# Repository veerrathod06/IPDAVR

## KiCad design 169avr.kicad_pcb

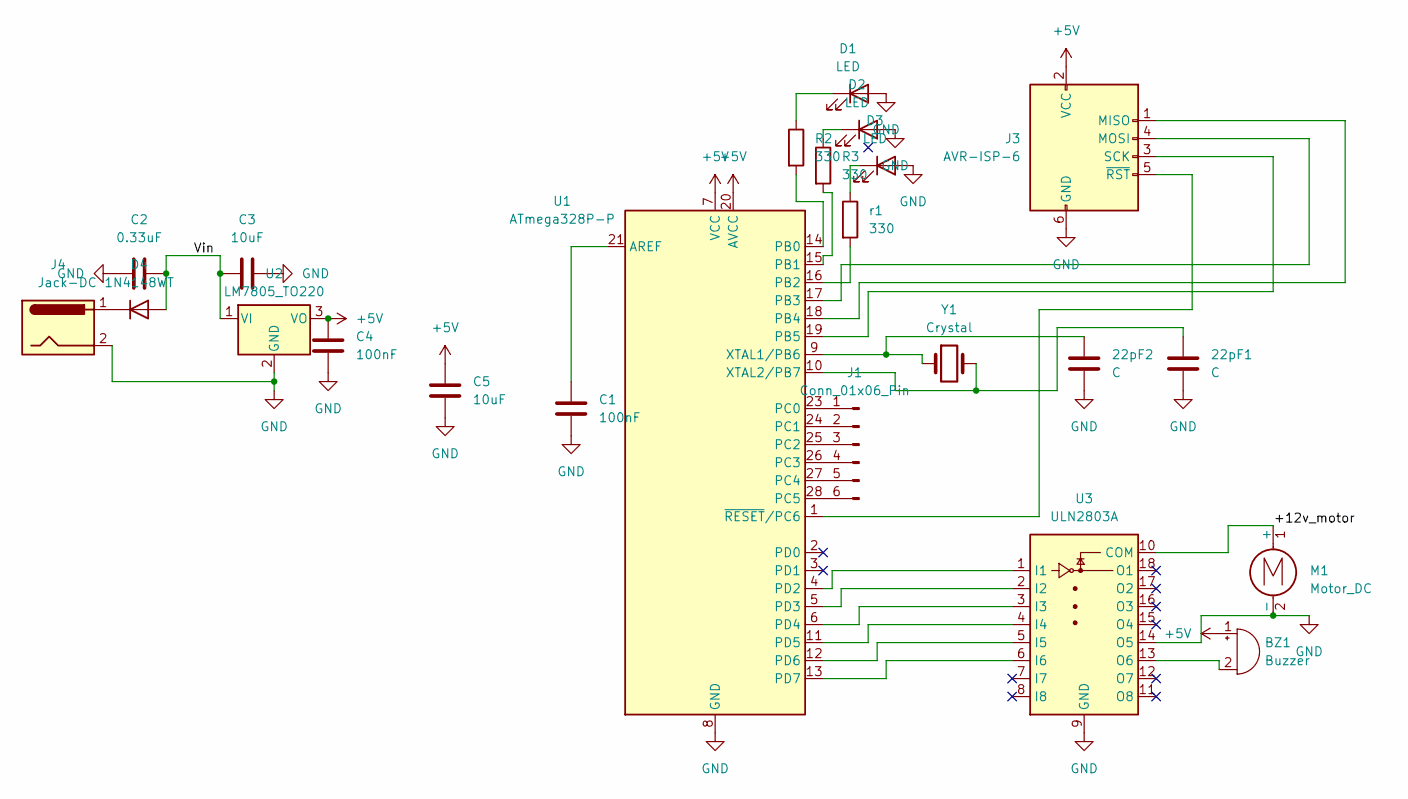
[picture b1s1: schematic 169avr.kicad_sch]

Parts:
22pF1, 22pF2: C; C_Disc_D5.0mm_W2.5mm_P5.00mm
BZ1: Buzzer; Buzzer_12x9.5RM7.6
C1, C4: 100nF; C_Disc_D5.0mm_W2.5mm_P5.00mm
C2: 0.33uF; CP_Radial_D5.0mm_P2.00mm
C3, C5: 10uF; CP_Radial_D5.0mm_P2.00mm
D1, D2, D3: LED; LED_D5.0mm_IRBlack
D4: 1N4148WT; D_DO-35_SOD27_P7.62mm_Horizontal
J1: Conn_01x06_Pin; PinHeader_1x06_P2.54mm_Vertical
J3: AVR-ISP-6; PinHeader_2x03_P2.54mm_Vertical
J4: Jack-DC; BarrelJack_SwitchcraftConxall_RAPC10U_Horizontal
M1: Motor_DC; TerminalBlock_Phoenix_MKDS-1-2-3.81_1x02_P3.81mm_Horizontal
R2: 330; R_Axial_DIN0204_L3.6mm_D1.6mm_P1.90mm_Vertical
R3: 330; R_Axial_DIN0204_L3.6mm_D1.6mm_P2.54mm_Vertical
U1: ATmega328P-P; DIP-28_W7.62mm
U2: LM7805_TO220; TO-220-3_Vertical
U3: ULN2803A; DIP-18_W7.62mm
Y1: Crystal; Crystal_HC49-U_Vertical
r1: 330; R_Axial_DIN0207_L6.3mm_D2.5mm_P15.24mm_Horizontal

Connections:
+5V: BZ1.1 (+), C4.1, C5.1, J3.2 (VCC), U1.7 (VCC), U1.20 (AVCC), U2.3 (VO)
/+12v_motor: M1.1 (+), U3.10 (COM)
/Vin: C2.1, C3.1, D4.2 (A), U2.1 (VI)
GND: 22pF1.2, 22pF2.2, C1.2, C2.2, C3.2, C4.2, C5.2, D1.2 (A), D2.2 (A), D3.2 (A), J3.6 (GND), J4.2, M1.2 (-), U1.8 (GND), U1.22 (GND), U2.2 (GND), U3.9 (GND), U3.14 (O5)
unnamed: BZ1.2 (-), U3.13 (O6)
unnamed: D1.1 (K), R2.1
unnamed: D2.1 (K), R3.1
unnamed: D3.1 (K), r1.1
unnamed: D4.1 (K), J4.1
unnamed: J1.1, U1.23 (PC0)
unnamed: J1.2, U1.24 (PC1)
unnamed: J1.3, U1.25 (PC2)
unnamed: J1.4, U1.26 (PC3)
unnamed: J1.5, U1.27 (PC4)
unnamed: J1.6, U1.28 (PC5)
unnamed: J3.1 (MISO), U1.18 (PB4)
unnamed: J3.4 (MOSI), U1.17 (PB3)
unnamed: J3.3 (SCK), U1.19 (PB5)
unnamed: J3.5 (~RST), U1.1 (~RESET/PC6)
unnamed: C1.1, U1.21 (AREF)
unnamed: R2.2, U1.14 (PB0)
unnamed: R3.2, U1.15 (PB1)
unnamed: U1.16 (PB2), r1.2
unnamed: U1.4 (PD2), U3.1 (I1)
unnamed: U1.5 (PD3), U3.2 (I2)
unnamed: U1.6 (PD4), U3.3 (I3)
unnamed: U1.11 (PD5), U3.4 (I4)
unnamed: U1.12 (PD6), U3.5 (I5)
unnamed: U1.13 (PD7), U3.6 (I6)
unnamed: 22pF2.1, U1.9 (XTAL1/PB6), Y1.1
unnamed: 22pF1.1, U1.10 (XTAL2/PB7), Y1.2

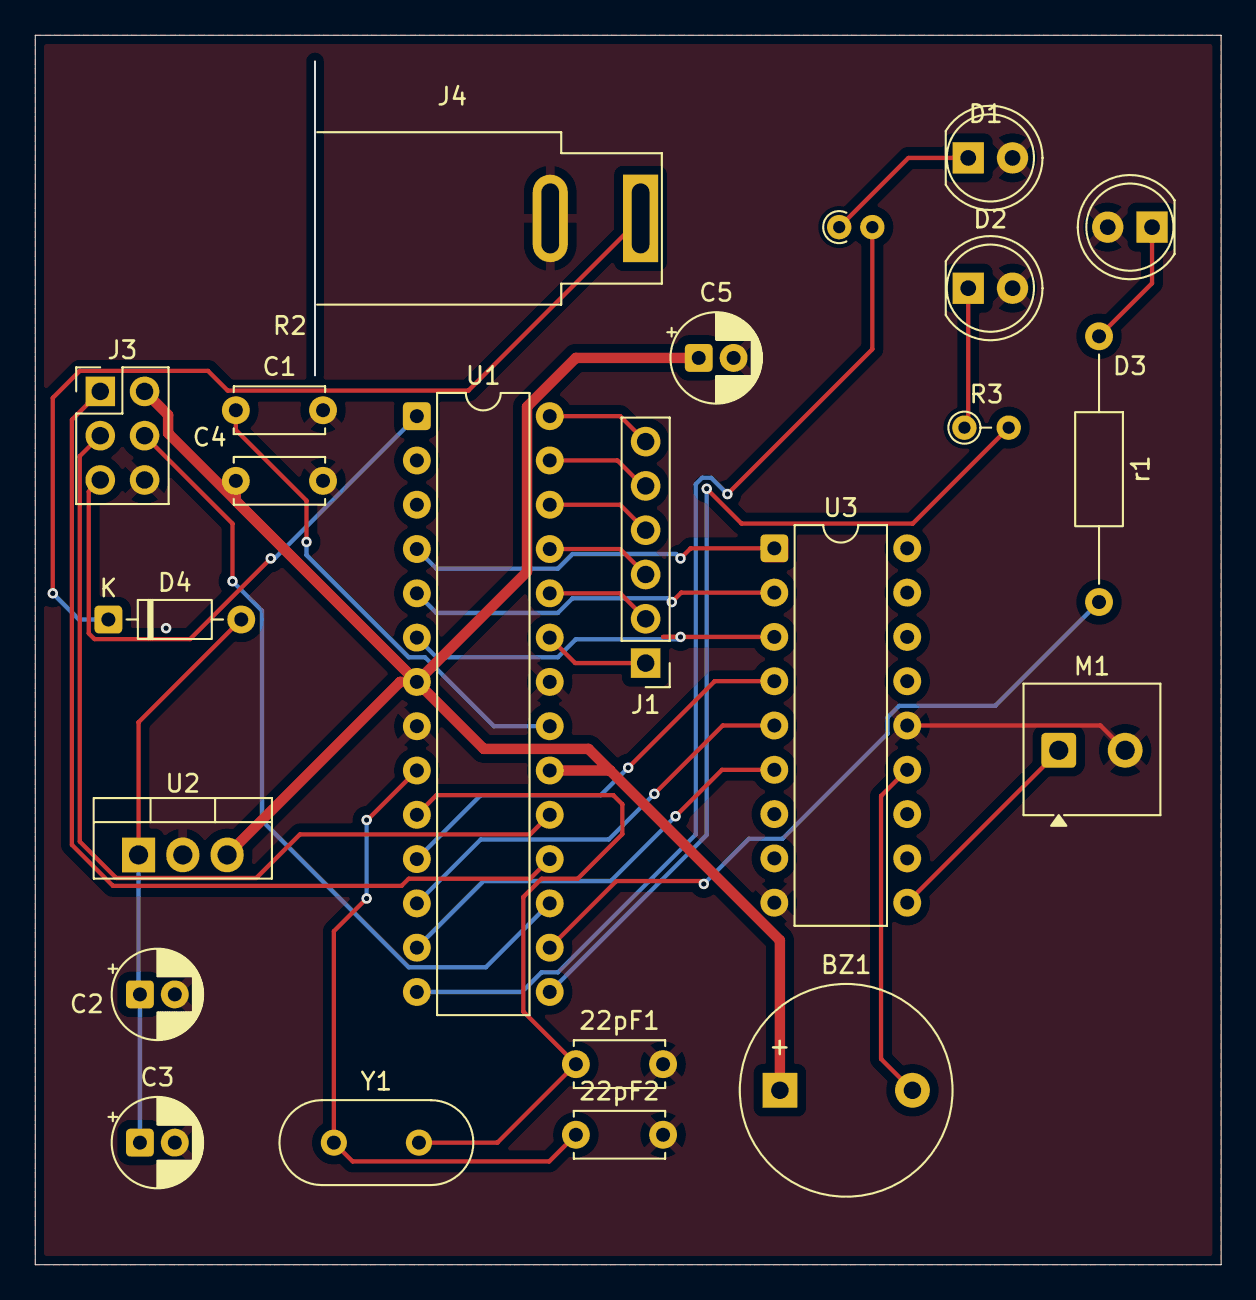
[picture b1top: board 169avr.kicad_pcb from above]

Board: 2 copper layers, 67.9 x 70.4 mm, 23 parts (0 on the bottom side), 31 nets.
